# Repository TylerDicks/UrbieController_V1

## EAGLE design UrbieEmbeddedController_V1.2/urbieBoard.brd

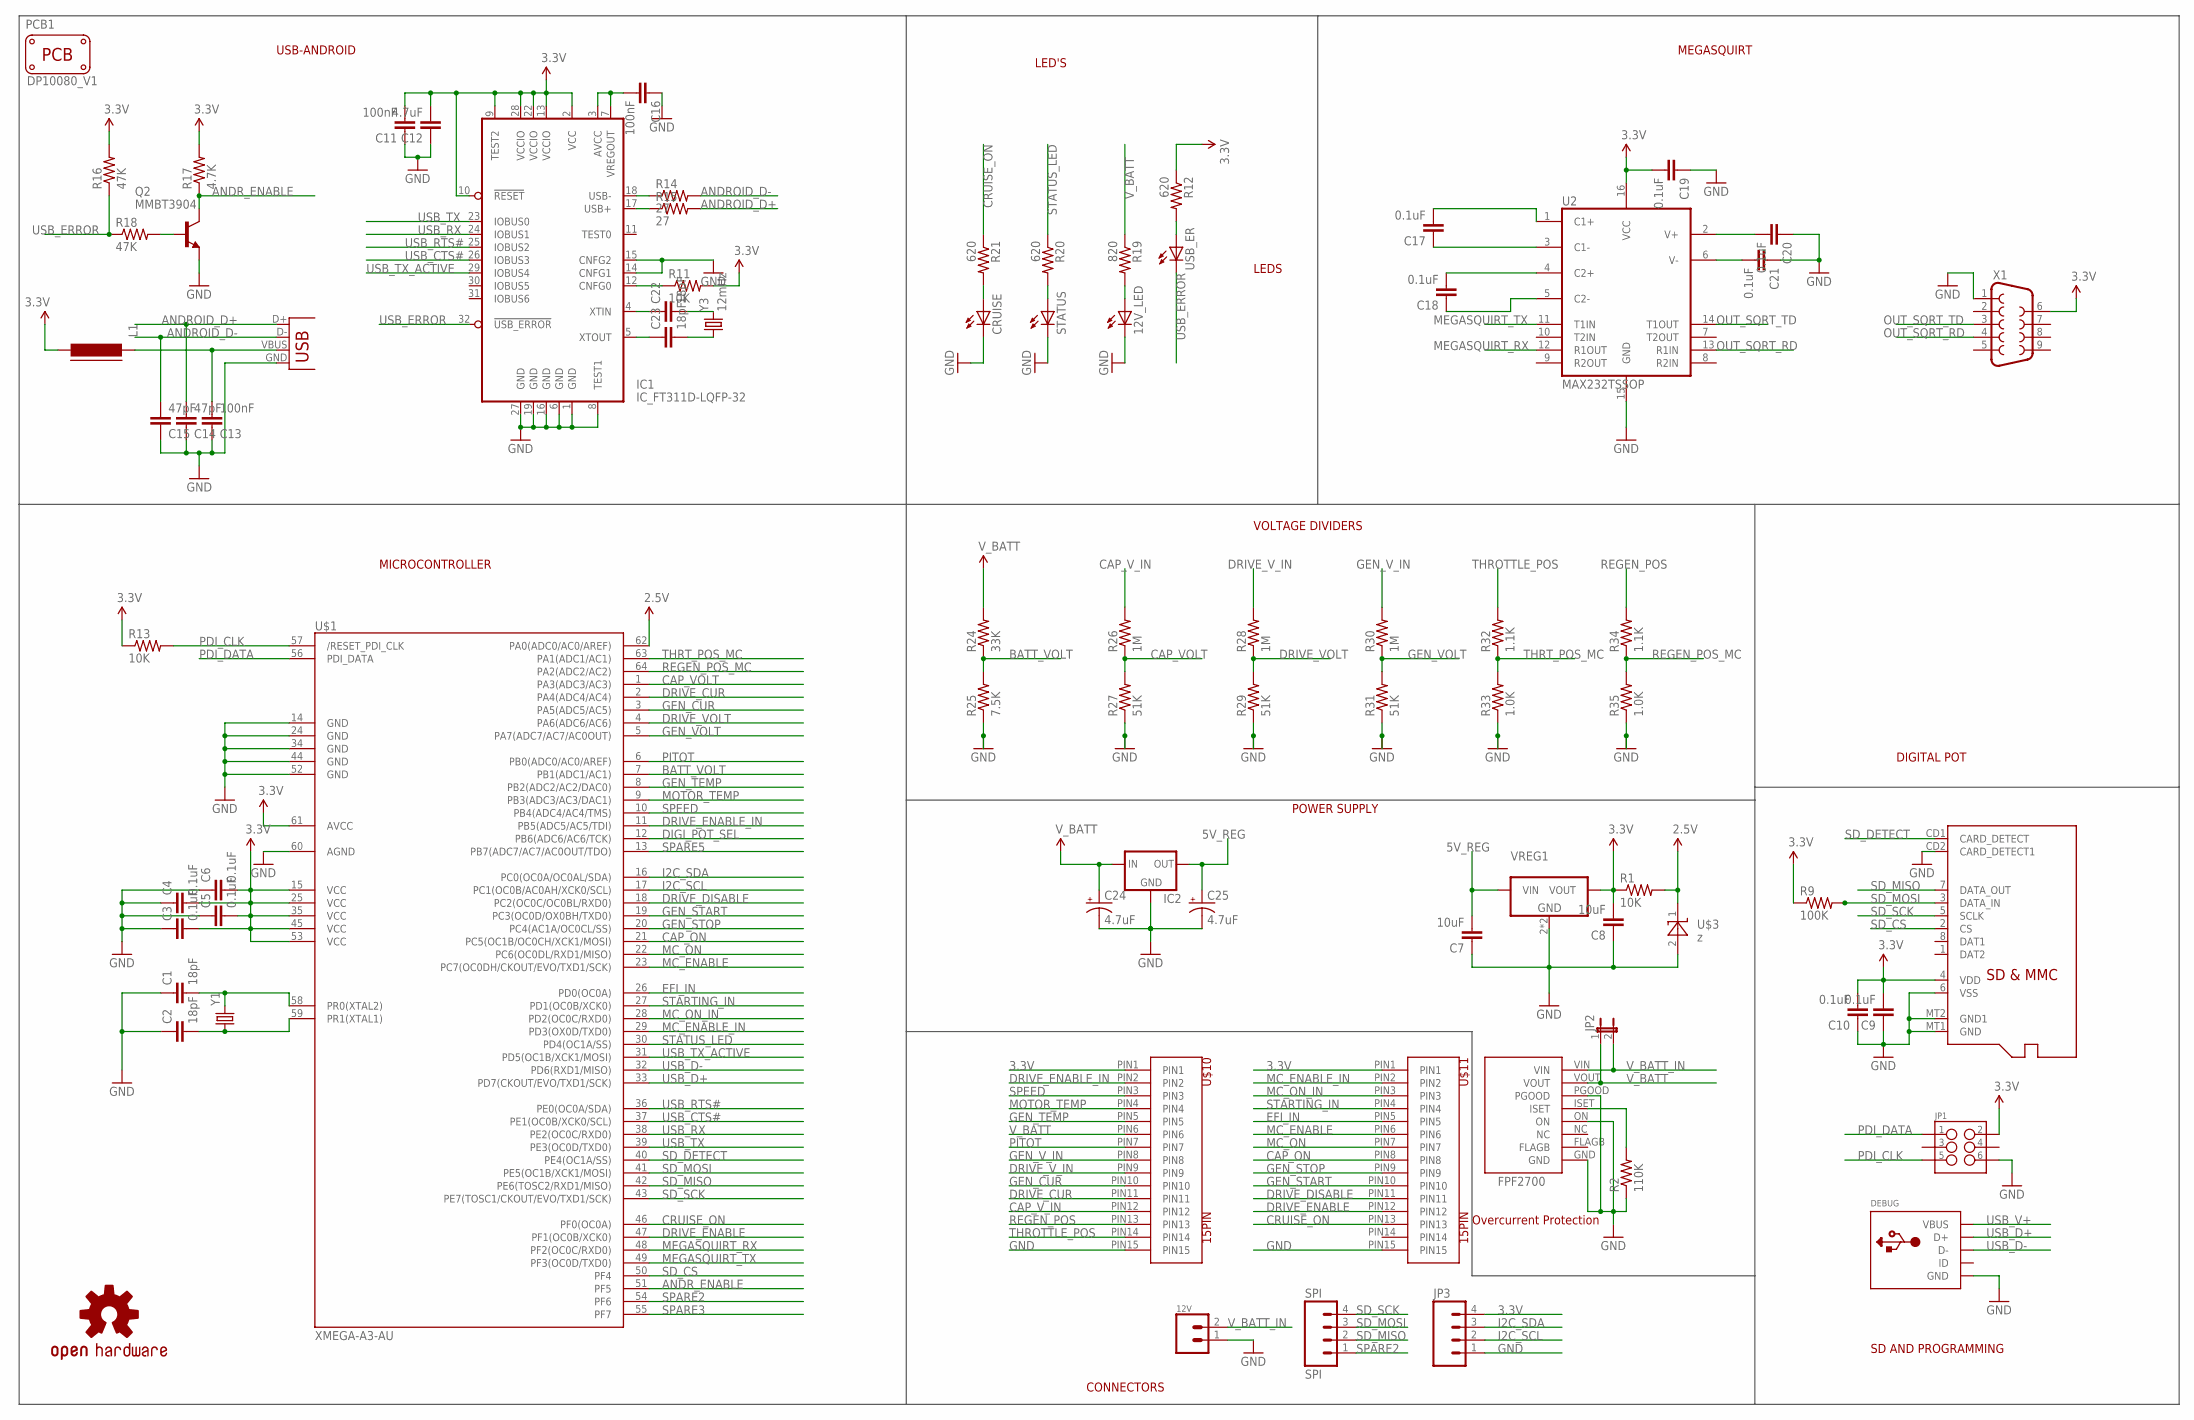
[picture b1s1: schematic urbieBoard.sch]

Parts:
12V: DURACLIK-2SMD; DURACLIK-2
12V_LED: LEDCHIP-LED0603; CHIP-LED0603
C1, C2, C22, C23: 18pF; 0603-CAP; MPN 06031A180JAT2A
C3, C4, C5, C6, C9, C10, C17, C18, C19, C20, C21: 0.1uF; 0603-CAP
C7, C8: 10uF; 0603-CAP
C11, C13, C16: 100nF; 0603-CAP
C12: 4.7uF; 0603-CAP
C14, C15: 47pF; 0603-CAP
C24, C25: 4.7uF; CPOL-RADIAL-10UF-25V
CRUISE: LEDCHIP-LED0603; CHIP-LED0603
DEBUG: USBMINIB; USB-MINIB
IC1: IC_FT311D-LQFP-32; LQFP-32
IC2: V_REG_78XXSINK; TO220-IGO
JP1: M03X22X3_SILK_SM; 2X3
JP2: JP1E; JP1
JP3: M04POLAR_LOCK; MOLEX-1X4_LOCK
JP4: USB-A-S
L1: FERRITE-0805; FB805
LOGO1: OSHW-LOGOM; OSHW-LOGO-M
PCB1: PCB_DP_RECTANGLE-80X100; DP10080_V1
Q2: MMBT3904; SOT23-BEC
R1, R11, R13: 10K; 0603-RES
R2: 110K; 0603-RES
R9: 100K; 0603-RES
R12, R20, R21: 620; 0603-RES
R14, R15: 27; 0603-RES
R16, R18: 47K; 0603-RES
R17: 4.7K; 0603-RES
R19: 820; 0603-RES
R24: 33K; 0603-RES
R25: 7.5K; 0603-RES
R26, R28, R30: 1M; 0603-RES
R27, R29, R31: 51K; 0603-RES
R32, R34: 1.1K; 0603-RES
R33, R35: 1.0K; 0603-RES
SPI: SPI; MOLEX-1X4_LOCK
STATUS: LEDCHIP-LED0603; CHIP-LED0603
U2: MAX232TSSOP; TSSOP16
U$1: XMEGA-A3-AU; TQFP64_14X14MM
U$2: MICROSD
U$3: z; SOT-23
U$8: FPF2700
U$10, U$11: 15PIN
USB_ER: LEDCHIP-LED0603; CHIP-LED0603
VREG1: VREG_3PINS-SOT-223; SOT-223
X1: DB9MALE; DB9_MALE
Y1: CRYSTALTXC-7A; CRYSTAL-TXC-7A
Y3: 12mHz; CRYSTAL-TXC-7A

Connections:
2.8V: R1.2, U$1.62 (PA0(ADC0/AC0/AREF)), U$3.1 (C)
3.3V: C3.2, C4.2, C5.2, C6.2, C8.2, C9.2, C10.2, C11.2, C12.2, C19.2, IC1.2 (VCC), IC1.9 (TEST2), IC1.10 (!RESET), IC1.13 (VCCIO), IC1.22 (VCCIO), IC1.28 (VCCIO), JP1.2, JP3.4, L1.2, R1.1, R9.1, R11.2, R12.1, R13.1, R16.2, R17.2, U2.16 (VCC), U$1.15 (VCC1), U$1.25 (VCC2), U$1.35 (VCC3), U$1.45 (VCC4), U$1.53 (VCC5), U$1.61 (AVCC), U$2.4 (VDD), U$10.PIN1, U$11.PIN1, VREG1.3 (VOUT), X1.6
5V_REG: C7.2, C25.1 (+), IC2.OUT, VREG1.1 (VIN)
ANDROID_D+: C14.2, JP4.D+, R15.2
ANDROID_D-: C15.2, JP4.D-, R14.2
ANDR_ENABLE: Q2.C, R17.1, U$1.51 (PF5)
BATT_VOLT: R24.1, R25.2, U$1.7 (PB1(ADC1/AC1))
CAP_ON: U$1.21 (PC5(OC1B/OC0CH/XCK1/MOSI)), U$11.PIN8
CAP_VOLT: R26.1, R27.2, U$1.1 (PA3(ADC3/AC3))
CAP_V_IN: R26.2, U$10.PIN12
CRUISE_ON: R21.1, U$1.46 (PF0(OC0A)), U$11.PIN13
DIGI_POT_SEL: U$1.12 (PB6(ADC6/AC6/TCK))
DRIVE_CUR: U$1.2 (PA4(ADC4/AC4)), U$10.PIN11
DRIVE_DISABLE: U$1.18 (PC2(OC0C/OC0BL/RXD0)), U$11.PIN11
DRIVE_ENABLE: U$1.47 (PF1(OC0B/XCK0)), U$11.PIN12
DRIVE_ENABLE_IN: U$1.11 (PB5(ADC5/AC5/TDI)), U$10.PIN2
DRIVE_VOLT: R28.1, R29.2, U$1.4 (PA6(ADC6/AC6))
DRIVE_V_IN: R28.2, U$10.PIN9
EFI_IN: U$1.26 (PD0(OC0A)), U$11.PIN5
GEN_CUR: U$1.3 (PA5(ADC5/AC5)), U$10.PIN10
GEN_START: U$1.19 (PC3(OC0D/OX0BH/TXD0)), U$11.PIN10
GEN_STOP: U$1.20 (PC4(AC1A/OC0CL/SS)), U$11.PIN9
GEN_TEMP: U$1.8 (PB2(ADC2/AC2/DAC0)), U$10.PIN5
GEN_VOLT: R30.1, R31.2, U$1.5 (PA7(ADC7/AC7/AC0OUT))
GEN_V_IN: R30.2, U$10.PIN8
GND: 12V.1 (PIN1), 12V_LED.C, C1.1, C2.1, C3.1, C4.1, C5.1, C6.1, C7.1, C8.1, C9.1, C10.1, C11.1, C12.1, C13.1, C14.1, C15.1, C16.1, C19.1, C20.1, C21.1, C24.2 (-), C25.2 (-), CRUISE.C, DEBUG.GND, IC1.1 (GND), IC1.6 (GND), IC1.8 (TEST1), IC1.14 (CNFG1), IC1.15 (CNFG2), IC1.16 (GND), IC1.19 (GND), IC1.27 (GND), IC2.GND, JP1.6, JP3.1, JP4.GND, Q2.E, R2.1, R25.1, R27.1, R29.1, R31.1, R33.1, R35.1, STATUS.C, U2.15 (GND), U$1.14 (GND1), U$1.24 (GND2), U$1.34 (GND3), U$1.44 (GND4), U$1.52 (GND5), U$1.60 (AGND), U$2.6 (VSS), U$2.CD2 (CARD_DETECT1), U$2.MT1 (GND), U$2.MT2 (GND1), U$3.2 (A), U$8.GND, U$8.ON, U$8.PGOOD, U$10.PIN15, U$11.PIN15, VREG1.2 (GND), VREG1.4 (GND), X1.1
I2C_SCL: JP3.2, U$1.17 (PC1(OC0B/AC0AH/XCK0/SCL))
I2C_SDA: JP3.3, U$1.16 (PC0(OC0A/OC0AL/SDA))
MC_ENABLE: U$1.23 (PC7(OC0DH/CKOUT/EVO/TXD1/SCK)), U$11.PIN6
MC_ENABLE_IN: U$1.29 (PD3(OX0D/TXD0)), U$11.PIN2
MC_ON: U$1.22 (PC6(OC0DL/RXD1/MISO)), U$11.PIN7
MC_ON_IN: U$1.28 (PD2(OC0C/RXD0)), U$11.PIN3
MEGASQUIRT_RX: U2.12 (R1OUT), U$1.48 (PF2(OC0C/RXD0))
MEGASQUIRT_TX: U2.11 (T1IN), U$1.49 (PF3(OC0D/TXD0))
MOTOR_TEMP: U$1.9 (PB3(ADC3/AC3/DAC1)), U$10.PIN4
unnamed: C1.2, U$1.58 (PR0(XTAL2)), Y1.P$2 (2)
unnamed: C2.2, U$1.59 (PR1(XTAL1)), Y1.P$1 (1)
unnamed: C22.1, IC1.4 (XTIN)
unnamed: C23.1, IC1.5 (XTOUT)
unnamed: R2.2, U$8.ISET
unnamed: IC1.12 (CNFG0), R11.1
unnamed: C22.2, Y3.P$2 (2)
unnamed: C23.2, Y3.P$1 (1)
unnamed: IC1.18 (USB-), R14.1
unnamed: C17.2, U2.1 (C1+)
unnamed: IC1.17 (USB+), R15.1
unnamed: C16.2, IC1.3 (AVCC), IC1.7 (VREGOUT)
unnamed: Q2.B, R18.2
unnamed: C13.2, JP4.VBUS, L1.1
unnamed: C17.1, U2.3 (C1-)
unnamed: C18.2, U2.4 (C2+)
unnamed: C18.1, U2.5 (C2-)
unnamed: C21.2, U2.6 (V-)
unnamed: C20.2, U2.2 (V+)
unnamed: R12.2, USB_ER.A
unnamed: 12V_LED.A, R19.2
unnamed: CRUISE.A, R21.2
unnamed: R20.2, STATUS.A
OUT_SQRT_RD: U2.13 (R1IN), X1.4
OUT_SQRT_TD: U2.14 (T1OUT), X1.3
PDI_CLK: JP1.5, R13.2, U$1.57 (/RESET_PDI_CLK)
PDI_DATA: JP1.1, U$1.56 (PDI_DATA)
PITOT: U$1.6 (PB0(ADC0/AC0/AREF)), U$10.PIN7
REGEN_POS: R34.2, U$10.PIN13
REGEN_POS_MC: R34.1, R35.2, U$1.64 (PA2(ADC2/AC2))
SD_CS: U$1.50 (PF4), U$2.2 (CS)
SD_DETECT: U$1.40 (PE4(OC1A/SS)), U$2.CD1 (CARD_DETECT)
SD_MISO: SPI.2, U$1.42 (PE6(TOSC2/RXD1/MISO)), U$2.7 (DATA_OUT)
SD_MOSI: R9.2, SPI.3, U$1.41 (PE5(OC1B/XCK1/MOSI)), U$2.3 (DATA_IN)
SD_SCK: SPI.4, U$1.43 (PE7(TOSC1/CKOUT/EVO/TXD1/SCK)), U$2.5 (SCLK)
SPARE2: SPI.1, U$1.54 (PF6)
SPARE3: U$1.55 (PF7)
SPARE5: U$1.13 (PB7(ADC7/AC7/AC0OUT/TDO))
SPEED: U$1.10 (PB4(ADC4/AC4/TMS)), U$10.PIN3
STARTING_IN: U$1.27 (PD1(OC0B/XCK0)), U$11.PIN4
STATUS_LED: R20.1, U$1.30 (PD4(OC1A/SS))
THROTTLE_POS: R32.2, U$10.PIN14
THRT_POS_MC: R32.1, R33.2, U$1.63 (PA1(ADC1/AC1))
USB_CTS#: IC1.26 (IOBUS3), U$1.37 (PE1(OC0B/XCK0/SCL))
USB_D+: DEBUG.D+, U$1.33 (PD7(CKOUT/EVO/TXD1/SCK))
USB_D-: DEBUG.D-, U$1.32 (PD6(RXD1/MISO))
USB_ERROR: IC1.32 (!USB_ERROR), R16.1, R18.1, USB_ER.C
USB_RTS#: IC1.25 (IOBUS2), U$1.36 (PE0(OC0A/SDA))
USB_RX: IC1.24 (IOBUS1), U$1.38 (PE2(OC0C/RXD0))
USB_TX: IC1.23 (IOBUS0), U$1.39 (PE3(OC0D/TXD0))
USB_TX_ACTIVE: IC1.29 (IOBUS4), U$1.31 (PD5(OC1B/XCK1/MOSI))
USB_V+: DEBUG.VBUS
V_BATT: C24.1 (+), IC2.IN, JP2.1, R19.1, R24.2, U$8.VOUT, U$10.PIN6
V_BATT_IN: 12V.2 (PIN2), JP2.2, U$8.VIN

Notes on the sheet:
MICROCONTROLLER
USB-ANDROID
MEGASQUIRT
POWER SUPPLY
VOLTAGE DIVIDERS
SD AND PROGRAMMING
CONNECTORS
DIGITAL POT
LEDS
LED'S
Overcurrent Protection

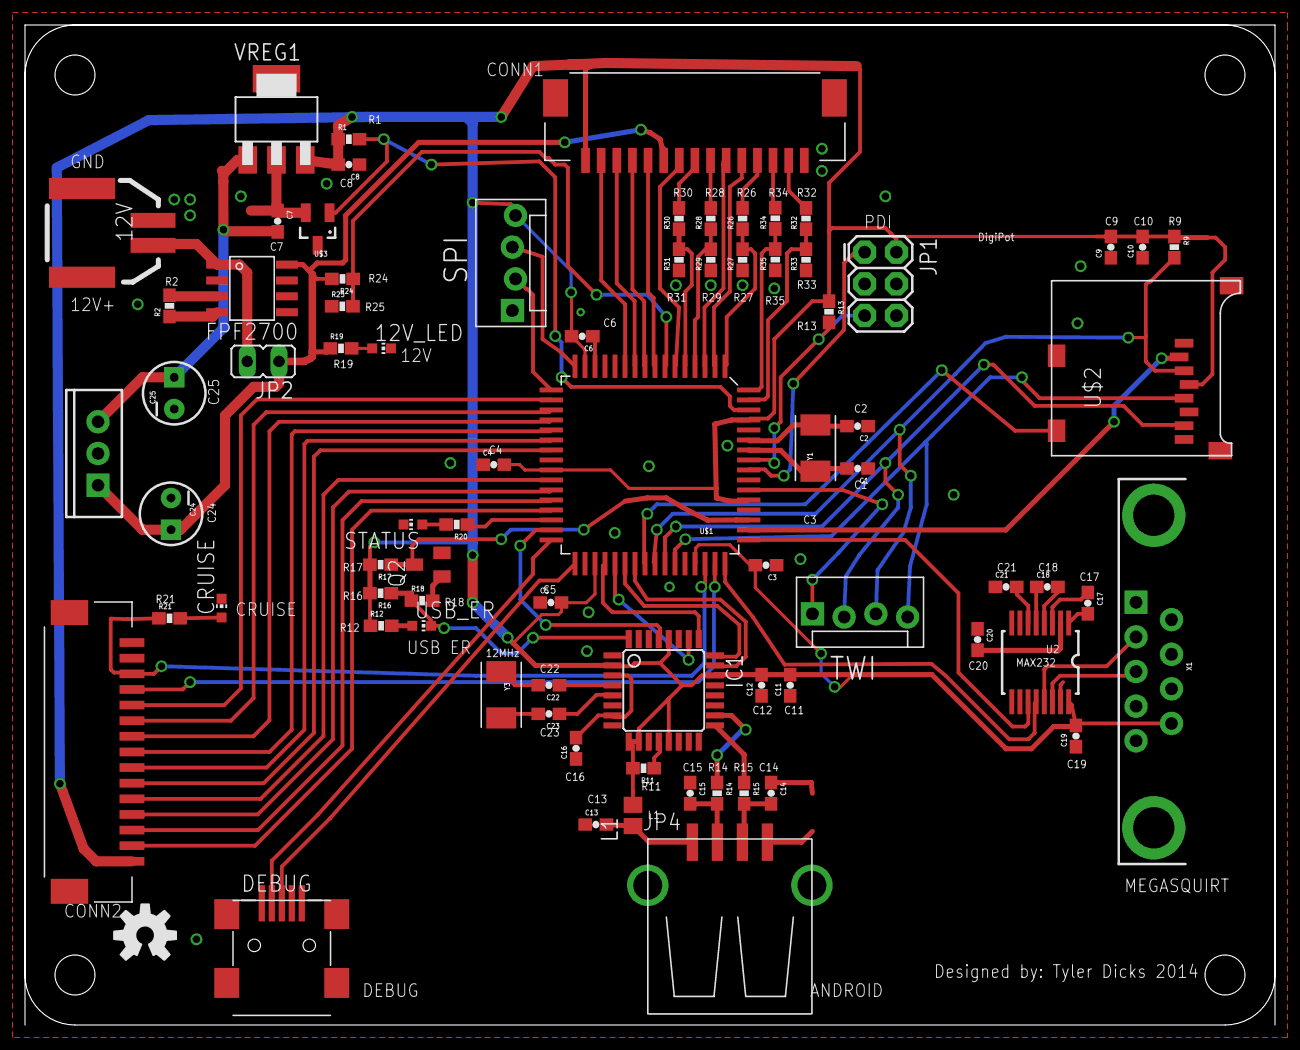
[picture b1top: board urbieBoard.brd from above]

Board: 2 copper layers, 100.0 x 80.0 mm, 82 parts (0 on the bottom side), 85 nets.

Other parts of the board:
U$4: SHELL
U$5: SEM
U$6: CU-PILLAR

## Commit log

2014-05-26 First Update
2014-06-03 Added Version 1.2
2014-07-11 Additions to Version 1.2
    Added the 12V to 5V regulator circuit
    Fixed SPI SS lines
    Added SPI Header
    Added TWI Header
    Added Silkscreen
    TODO: Adjust voltage divider values to get max 2.5V for ADCs
2014-07-11 Fixed ADC values and pin routing
    Fixed the voltage divider values to output 2.5V max signal voltage for
    ADC
2014-07-11 Added Top Level Visio Diagram and PDF
2014-07-11 small aesthetic fixes
2015-03-09 Gerbers and connector changes

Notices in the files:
parts and their libraries:
SparkFun-DigitalIC: Licensing: CC v3.0 Share-Alike You are welcome to use this library for commercial purposes.
